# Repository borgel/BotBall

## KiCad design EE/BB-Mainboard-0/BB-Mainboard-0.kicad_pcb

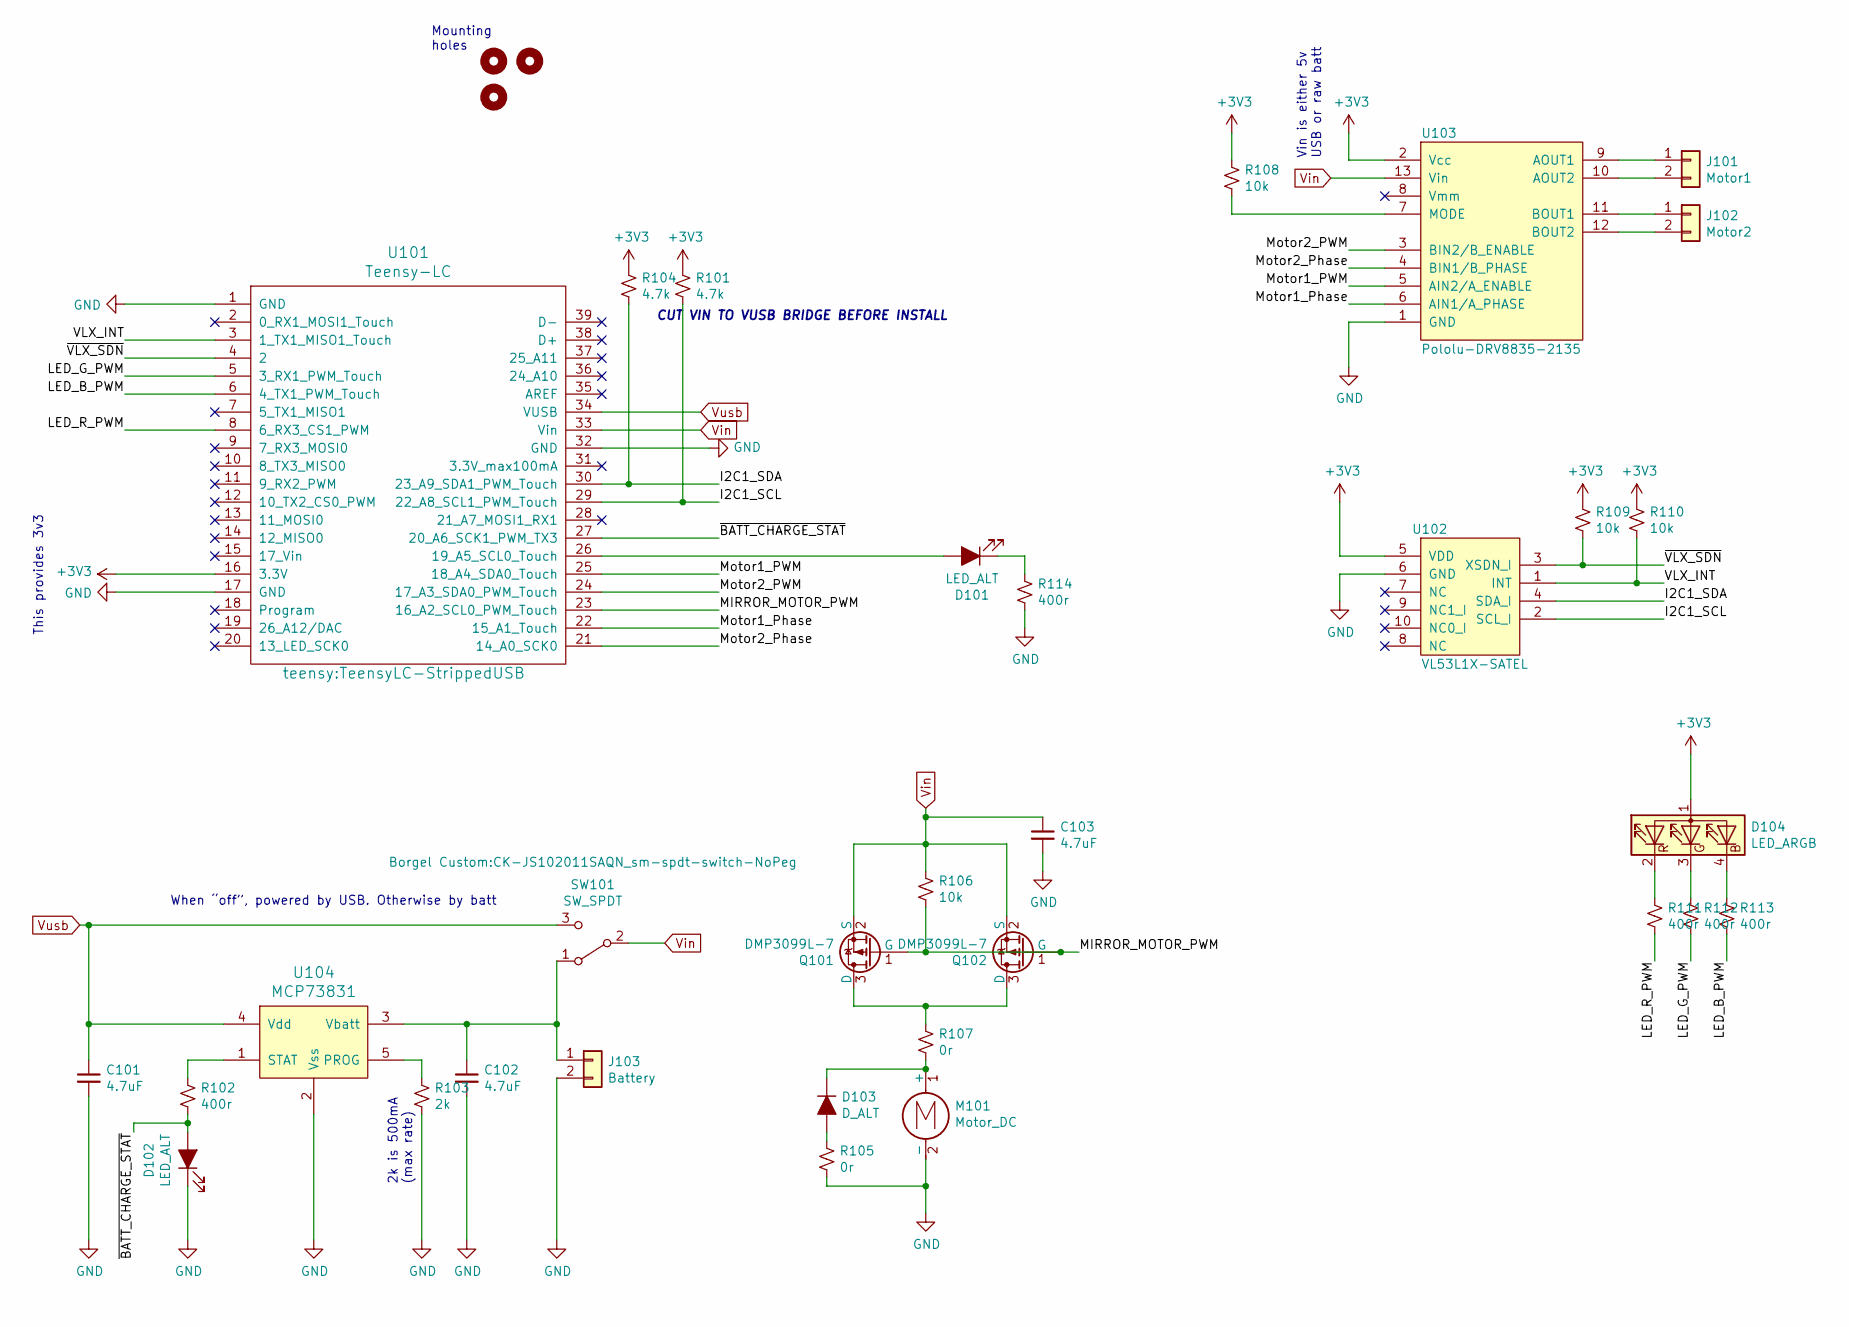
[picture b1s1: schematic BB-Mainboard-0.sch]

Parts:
C101, C102, C103: 4.7uF; C_0805_2012Metric
D101, D102: LED_ALT; LED_0603_SmallSilk
D103: D_ALT; D_0805_2012Metric
D104: LED_ARGB; LED_Kingbright_AAA3528ESGCT
H101, H102, H103: MountingHole; MountingHole_2.2mm_M2
J101: Motor1; PinSocket_1x02_P2.54mm_Vertical
J102: Motor2; PinSocket_1x02_P2.54mm_Vertical
J103: Battery; PinSocket_1x02_P2.54mm_Vertical
M101: Motor_DC; PinSocket_1x02_P2.54mm_Vertical
Q101, Q102: DMP3099L-7; SOT-23; DigiKey DMP3099L-7DICT-ND
R101, R104: 4.7k; R_0805_2012Metric
R102, R111, R112, R113, R114: 400r; R_0805_2012Metric
R103: 2k; R_0805_2012Metric
R105: 0r; R_0805_2012Metric
R106, R108, R109, R110: 10k; R_0805_2012Metric
R107: 0r; R_1206_3216Metric
SW101: SW_SPDT; CK-JS102011SAQN_sm-spdt-switch-NoPeg
U101: Teensy-LC; TeensyLC-StrippedUSB
U102: VL53L1X-SATEL; PinSocket_2x05_P2.54mm_Vertical
U103: Pololu-DRV8835-2135; Pololu-DRV8835-Carrier
U104: MCP73831; SOT-23-5

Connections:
+3V3: D104.1 (A), R101.1, R104.1, R108.2, R109.2, R110.2, U101.16 (3.3V), U102.5 (VDD), U103.2 (Vcc)
/I2C1_SCL: R101.2, U101.29 (22_A8_SCL1_PWM_Touch), U102.2 (SCL_I)
/I2C1_SDA: R104.2, U101.30 (23_A9_SDA1_PWM_Touch), U102.4 (SDA_I)
/LED_B_PWM: R113.1, U101.6 (4_TX1_PWM_Touch)
/LED_G_PWM: R112.1, U101.5 (3_RX1_PWM_Touch)
/LED_R_PWM: R111.1, U101.8 (6_RX3_CS1_PWM)
/MIRROR_MOTOR_PWM: Q101.1 (G), Q102.1 (G), R106.1, U101.23 (16_A2_SCL0_PWM_Touch)
/Motor1_PWM: U101.25 (18_A4_SDA0_Touch), U103.5 (AIN2/A_ENABLE)
/Motor1_Phase: U101.22 (15_A1_Touch), U103.6 (AIN1/A_PHASE)
/Motor2_PWM: U101.24 (17_A3_SDA0_PWM_Touch), U103.3 (BIN2/B_ENABLE)
/Motor2_Phase: U101.21 (14_A0_SCK0), U103.4 (BIN1/B_PHASE)
/VLX_INT: R110.1, U101.3 (1_TX1_MISO1_Touch), U102.1 (INT)
/~BATT_CHARGE_STAT: D102.2 (A), R102.2, U101.27 (20_A6_SCK1_PWM_TX3)
/~VLX_SDN: R109.1, U101.4 (2), U102.3 (XSDN_I)
GND: C101.2, C102.2, C103.2, D102.1 (K), J103.2, M101.2 (-), R103.2, R105.1, R114.1, U101.1 (GND), U101.17 (GND), U101.32 (GND), U102.6 (GND), U103.1 (GND), U103.14 (GND), U104.2 (Vss)
unnamed: C102.1, J103.1, SW101.1 (A), U104.3 (Vbatt)
unnamed: D101.1 (K), R114.2
unnamed: D101.2 (A), U101.26 (19_A5_SCL0_Touch)
unnamed: D103.1 (K), M101.1 (+), R107.1
unnamed: D103.2 (A), R105.2
unnamed: D104.2 (RK), R111.2
unnamed: D104.3 (GK), R112.2
unnamed: D104.4 (BK), R113.2
unnamed: J101.1, U103.9 (AOUT1)
unnamed: J101.2, U103.10 (AOUT2)
unnamed: J102.1, U103.11 (BOUT1)
unnamed: J102.2, U103.12 (BOUT2)
unnamed: Q101.3 (D), Q102.3 (D), R107.2
unnamed: R102.1, U104.1 (STAT)
unnamed: R103.1, U104.5 (PROG)
unnamed: R108.1, U103.7 (MODE)
Vin: C103.1, Q101.2 (S), Q102.2 (S), R106.2, SW101.2 (B), U101.33 (Vin), U103.13 (Vin)
Vusb: C101.1, SW101.3 (C), U101.34 (VUSB), U104.4 (Vdd)

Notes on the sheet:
2k is 500mA (max rate)
When “off”, powered by USB. Otherwise by batt
CUT VIN TO VUSB BRIDGE BEFORE INSTALL
This provides 3v3
Vin is either 5v USB or raw batt
Mounting holes

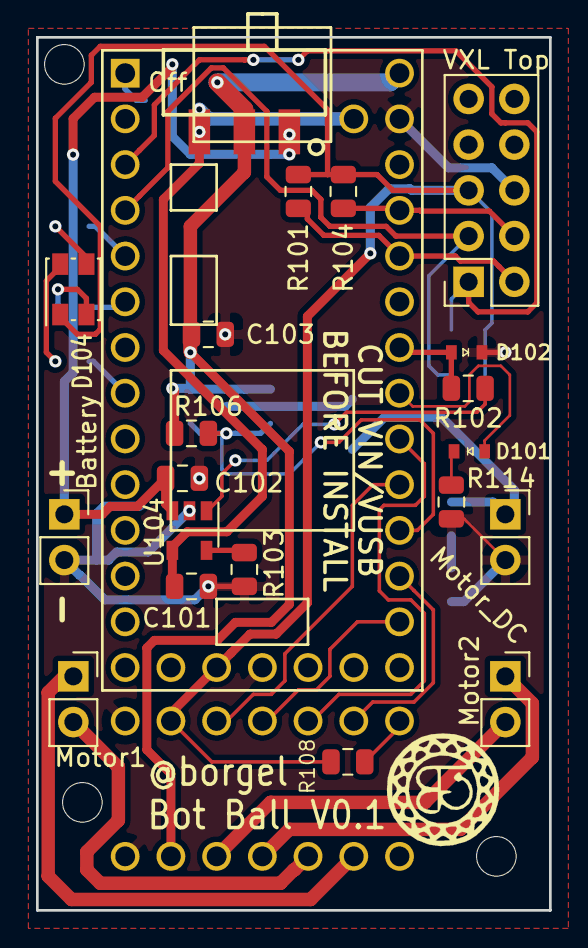
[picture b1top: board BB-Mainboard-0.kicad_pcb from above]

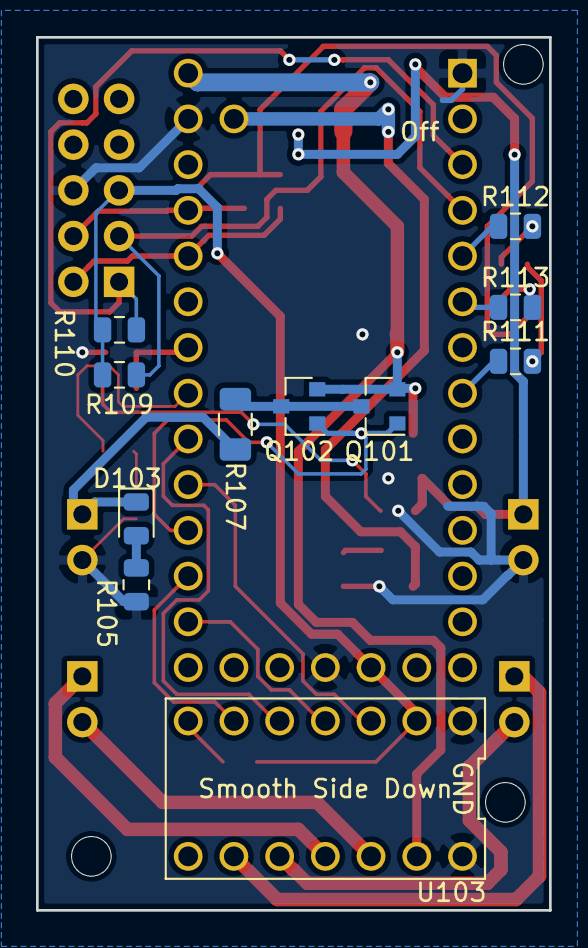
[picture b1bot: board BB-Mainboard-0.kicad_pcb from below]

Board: 2 copper layers, 28.5 x 48.5 mm, 35 parts (11 on the bottom side), 33 nets.

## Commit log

2019-10-07 Initial config of lots of things
2019-10-07 Update IOs
2019-10-27 IDE stuff
2019-10-27 Move source into dirs
2019-10-27 Stub real FW
2019-10-28 Update pin assignments
2019-10-28 Add RGB LED
2019-10-29 Proof of concept open-drain PWM
2019-10-29 WIP encapsulate open drain PWM
2019-11-01 LIDAR works!
2019-11-01 Push LIDAR into a separate module
2019-11-08 Early draft of homing routine
2019-11-08 Starting to cleanup homing
2019-11-09 Better filtering on distance measurements
2019-11-09 Slightly speed things up
2019-11-09 Move some HW defs into headers
2019-11-09 Calculate more scan parameters
2019-11-09 Don't store unneeded global var
2019-11-09 WIP real scan algorithm
2019-11-09 Adjusting algo
2019-11-10 Use fast GPIO in PWM CB
2019-11-10 Adjusting main loop logic
2019-11-10 Rework getDistance and backstop criteria
2019-11-10 OH MY GOD IT CAN SEE!
2019-11-10 Support two SPAD thresholds, play with timing
2019-11-10 Calibrate crosstalk
2019-11-10 Allow PWM to be paused and resumed
2019-11-10 More mirror and module tuning
2019-11-10 Start navigation module
2019-11-10 WIP v1 navigation
2019-11-10 Find targets for real
2019-11-10 Drives forward! Tweaking speeds
2019-11-14 Trim motors to drive approximately straight
2019-11-14 React if we don't see any targets for a while
2019-11-14 It works poorly, but it works!
2019-11-14 Dumber, better turns
2019-11-15 Remove old test FW
2019-11-15 Add chassis STLs
2019-11-15 Add EE sources
